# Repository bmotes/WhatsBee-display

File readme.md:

# whatsbee-display
Nodo de <a href="www.whatsbee.net">whatsbee</a> con una pantalla OLED de 0,96'', un pulsador y un led.
### Más información
http://blog.whatsbee.net/2016/08/sin-saber-muy-bien-porque/

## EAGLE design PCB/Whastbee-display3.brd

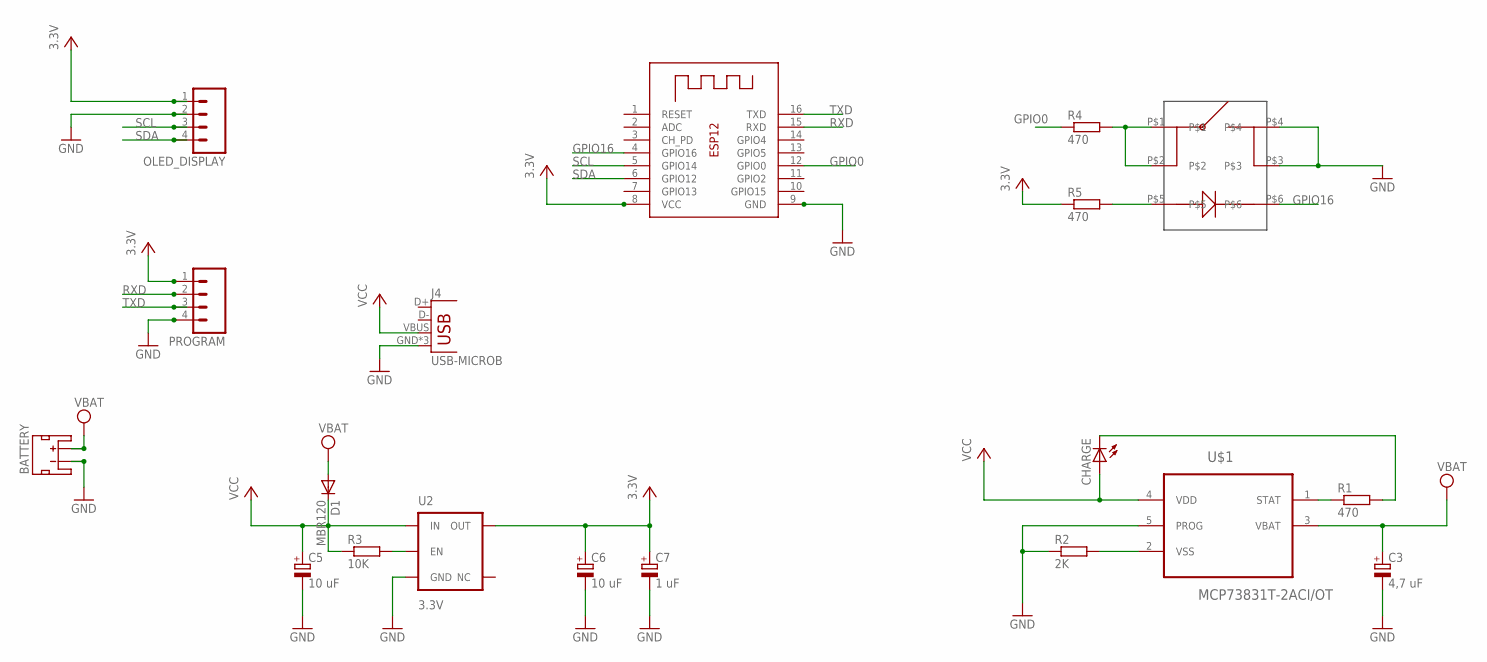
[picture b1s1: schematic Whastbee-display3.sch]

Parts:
BATTERY: JST_2MM_MALE; JST-2-SMD
C3: 4,7 uF; T/3528-12R
C5, C6: 10 uF; T/3528-12R
C7: 1 uF; T/3528-12R
CHARGE: LEDCHIPLED_0805; CHIPLED_0805
D1: MBR120; SOD-123_MINI-SMA
ESP8266-12: ESP-12
J4: USB-MICROB
OLED_DISPLAY: M04PTH; 1X04
PROGRAM: M04LOCK; 1X04_LOCK
R1, R4, R5: 470; R0805
R2: 2K; R0805
R3: 10K; R0805
U2: 3.3V; SOT23-5
U$1: MCP73831T-2ACI/OT; SOT95P280X145-5N
U$2: SWITCH-LED_AMIDATA; LED

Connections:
3.3V: C6.+, C7.+, ESP8266-12.8 (VCC), OLED_DISPLAY.1, PROGRAM.1, R5.1, U2.5 (OUT)
GND: BATTERY.1 (-), C3.-, C5.-, C6.-, C7.-, ESP8266-12.9 (GND), J4.GND, J4.MT1 (GND), J4.MT2 (GND), OLED_DISPLAY.2, PROGRAM.4, R2.1, U2.2 (GND), U$1.5 (PROG), U$2.P$3, U$2.P$4
GPIO0: ESP8266-12.12 (GPIO0), R4.1
GPIO16: ESP8266-12.4 (GPIO16), U$2.P$6
unnamed: R5.2, U$2.P$5
unnamed: R2.2, U$1.2 (VSS)
unnamed: R1.1, U$1.1 (STAT)
unnamed: CHARGE.C, R1.2
unnamed: R3.2, U2.3 (EN)
PS1: R4.2, U$2.P$1, U$2.P$2
RXD: ESP8266-12.15 (RXD), PROGRAM.2
SCL: ESP8266-12.5 (GPIO14), OLED_DISPLAY.3
SDA: ESP8266-12.6 (GPIO12), OLED_DISPLAY.4
TXD: ESP8266-12.16 (TXD), PROGRAM.3
VBAT: BATTERY.2 (+), C3.+, D1.A, U$1.3 (VBAT)
VCC: C5.+, CHARGE.A, D1.C, J4.VBUS, R3.1, U2.1 (IN), U$1.4 (VDD)

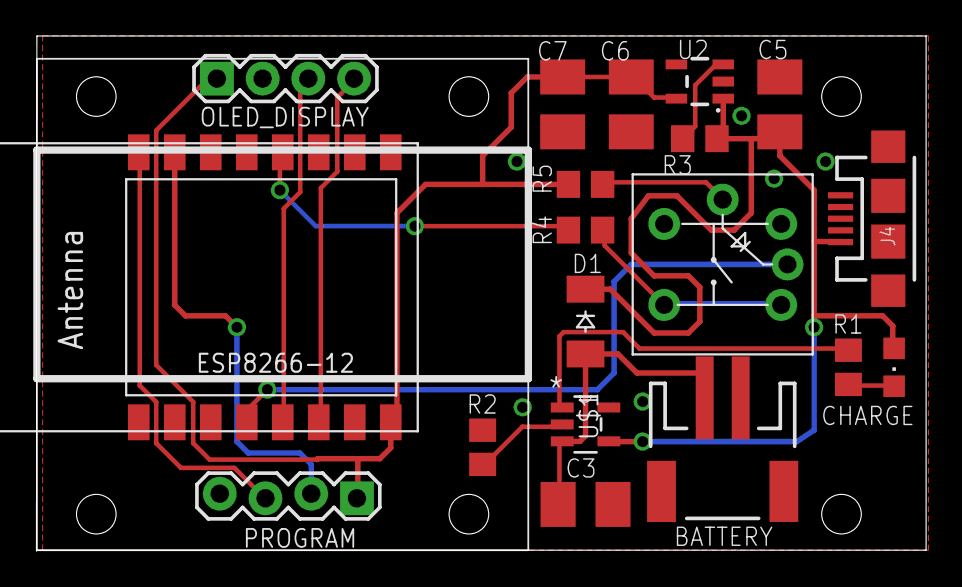
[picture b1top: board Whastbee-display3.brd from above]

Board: 2 copper layers, 49.4 x 28.5 mm, 19 parts (0 on the bottom side), 16 nets.

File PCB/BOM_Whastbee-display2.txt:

Partlist exported from C:/Users/crodriguez.BMOTES/Documents/eagle/WhatsBee_Diaplay/Whastbee-display2.sch at 09/08/2016 0:17

Part         Value              Device             Package          Description                                 BTM_NEG BTM_POS PROD_ID    SPICEMODEL SPICEPREFIX TOP_NEG TOP_POS VALUE
BATTERY                         JST_2MM_MALE       JST-2-SMD        Mates to single-cell LiPo batteries.        -       +       CONN-11443                        -       +            
C3           4,7 uF             CPOL-EUT/3528-12R  T/3528-12R       POLARIZED CAPACITOR, European symbol                                                                               
C5           10 uF              CPOL-EUT/3528-12R  T/3528-12R       POLARIZED CAPACITOR, European symbol                                                                               
C6           10 uF              CPOL-EUT/3528-12R  T/3528-12R       POLARIZED CAPACITOR, European symbol                                                                               
C7           1 uF               CPOL-EUT/3528-12R  T/3528-12R       POLARIZED CAPACITOR, European symbol                                                                               
CHARGE                          LEDCHIPLED_0805    CHIPLED_0805     LED                                                                                                                
D1           MBR120             CGRM4001-G         SOD-123_MINI-SMA Molded plasitc,JEDEC SOD-123/Mini SMA                                                                              
ESP8266-12                      ESP-12             ESP-12                                                                                                                              
J4           USB-MICROB         USB-MICROB         USB-MICROB       USB Connectors                                              CONN-09505                                             
OLED_DISPLAY                    M04PTH             1X04             Header 4                                                    CONN-09696                                             
PROGRAM                         M04LOCK            1X04_LOCK        Header 4                                                    CONN-09696                                             
R1           470                R                  R0805            RESISTOR, European symbol                                              NONE       R                                
R2           2K                 R                  R0805            RESISTOR, European symbol                                              NONE       R                                
R3           10K                R                  R0805            RESISTOR, European symbol                                              NONE       R                                
R4           470                R                  R0805            RESISTOR, European symbol                                              NONE       R                                
R5           470                R                  R0805            RESISTOR, European symbol                                              NONE       R                                
U$1          MCP73831T-2ACI/OT  MCP73831T-2ACI/OT  SOT95P280X145-5N Charge Management Controller                                                                                       
U$2          SWITCH-LED_AMIDATA SWITCH-LED_AMIDATA LED                                                                                                                                 
U2           3.3V               V_REG_AP2112K-3.3V SOT23-5          AP2112 - 600mA CMOS LDO Regulator w/ Enable                 VREG-12457                                        3.3V

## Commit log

2016-08-22 Version 0,1

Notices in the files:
parts and their libraries:
SparkFun-PowerIC: Licensing: Creative Commons ShareAlike 4.0 International - https://creativecommons.org/licenses/by-sa/4.0
